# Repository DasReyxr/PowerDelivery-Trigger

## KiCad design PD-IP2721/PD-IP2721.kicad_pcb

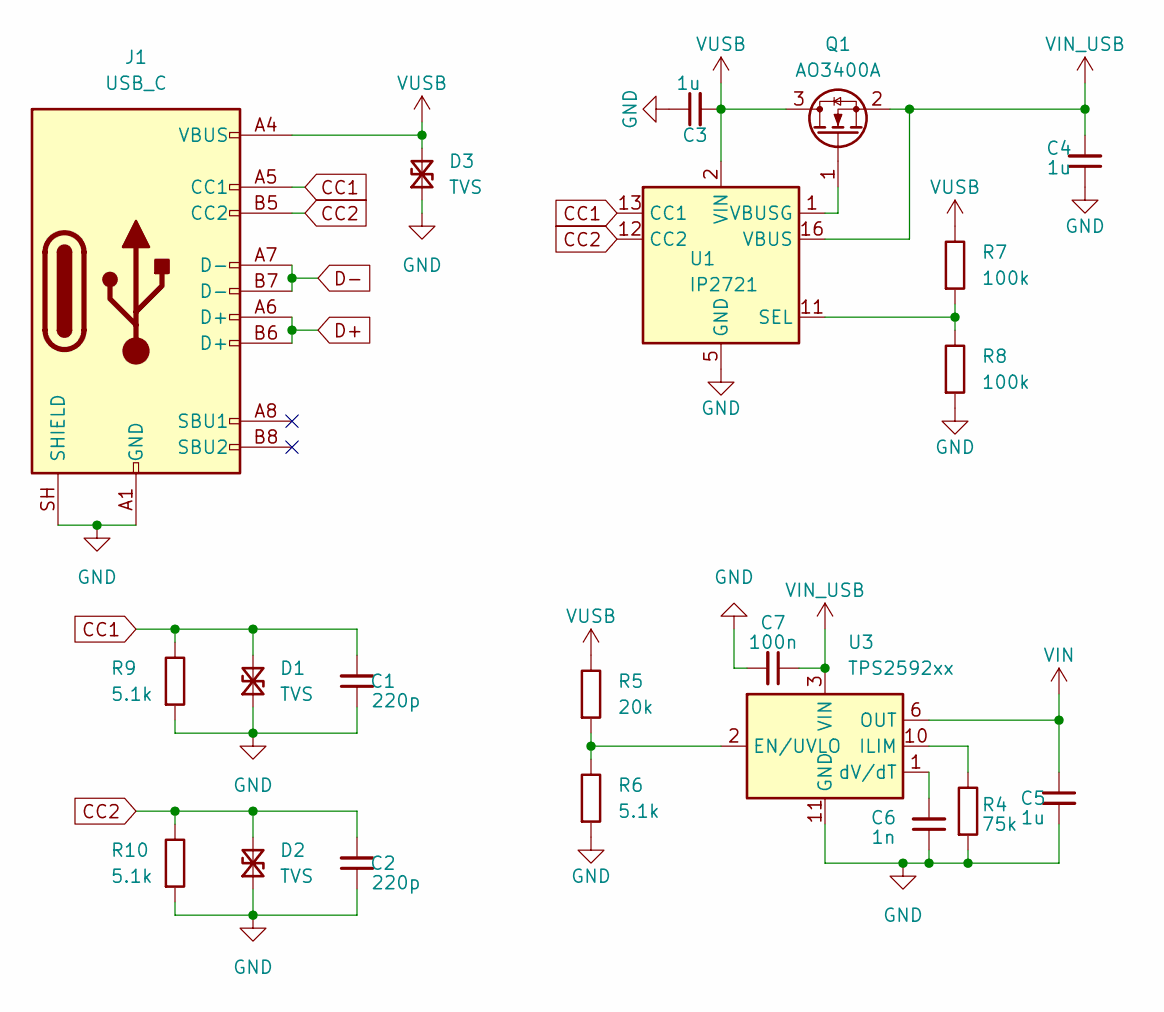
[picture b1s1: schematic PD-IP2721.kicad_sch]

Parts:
C1, C2: 220p; C_0603
C3, C4, C5: 1u; C_0603
C6: 1n; C_0603
C7: 100n; C_0603
D1, D2, D3: TVS; D_SOD-323
J1: USB_C; USB_C_Receptacle_JAE_DX07S016JA1R1500
Q1: AO3400A; SOT-23
R4: 75k; R_0603_1608Metric
R5: 20k; R_0603_1608Metric
R6, R9, R10: 5.1k; R_0603_1608Metric
R7, R8: 100k; R_0603_1608Metric
U1: IP2721; TSSOP-16_4.4x5mm_P0.65mm
U3: TPS2592xx; VSON-10-1EP_3x3mm_P0.5mm_EP1.65x2.4mm_ThermalVias

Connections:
CC1: C1.2, D1.2 (A2), J1.A5 (CC1), R9.2, U1.13 (CC1)
CC2: C2.2, D2.2 (A2), J1.B5 (CC2), R10.2, U1.12 (CC2)
D+: J1.A6 (D+), J1.B6 (D+)
D-: J1.A7 (D-), J1.B7 (D-)
GND: C1.1, C2.1, C3.1, C4.1, C5.2, C6.1, C7.2, D1.1 (A1), D2.1 (A1), D3.1 (A1), J1.A1 (GND), J1.A12 (GND), J1.B1 (GND), J1.B12 (GND), J1.SH (SHIELD), R4.1, R6.1, R8.1, R9.1, R10.1, U1.5 (GND), U3.11 (GND)
unnamed: Q1.1 (G), U1.1 (VBUSG)
unnamed: R7.1, R8.2, U1.11 (SEL)
unnamed: R5.1, R6.2, U3.2 (EN/UVLO)
unnamed: R4.2, U3.10 (ILIM)
unnamed: C6.2, U3.1 (dV/dT)
VIN: C5.1, U3.6 (OUT), U3.7 (OUT), U3.8 (OUT)
VIN_USB: C4.2, C7.1, Q1.2 (S), U1.16 (VBUS), U3.3 (VIN), U3.4 (VIN), U3.5 (VIN)
VUSB: C3.2, D3.2 (A2), J1.A4 (VBUS), J1.A9 (VBUS), J1.B4 (VBUS), J1.B9 (VBUS), Q1.3 (D), R5.2, R7.2, U1.2 (VIN)

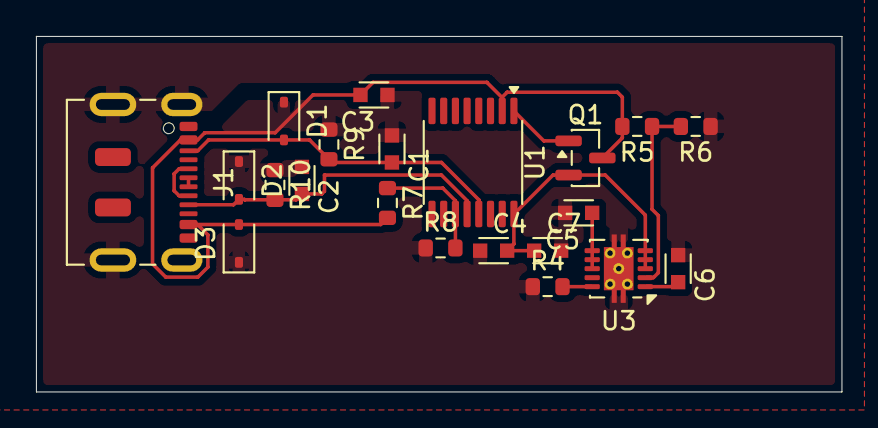
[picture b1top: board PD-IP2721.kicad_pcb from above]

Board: 2 copper layers, 44.8 x 19.8 mm, 21 parts (0 on the bottom side), 13 nets.

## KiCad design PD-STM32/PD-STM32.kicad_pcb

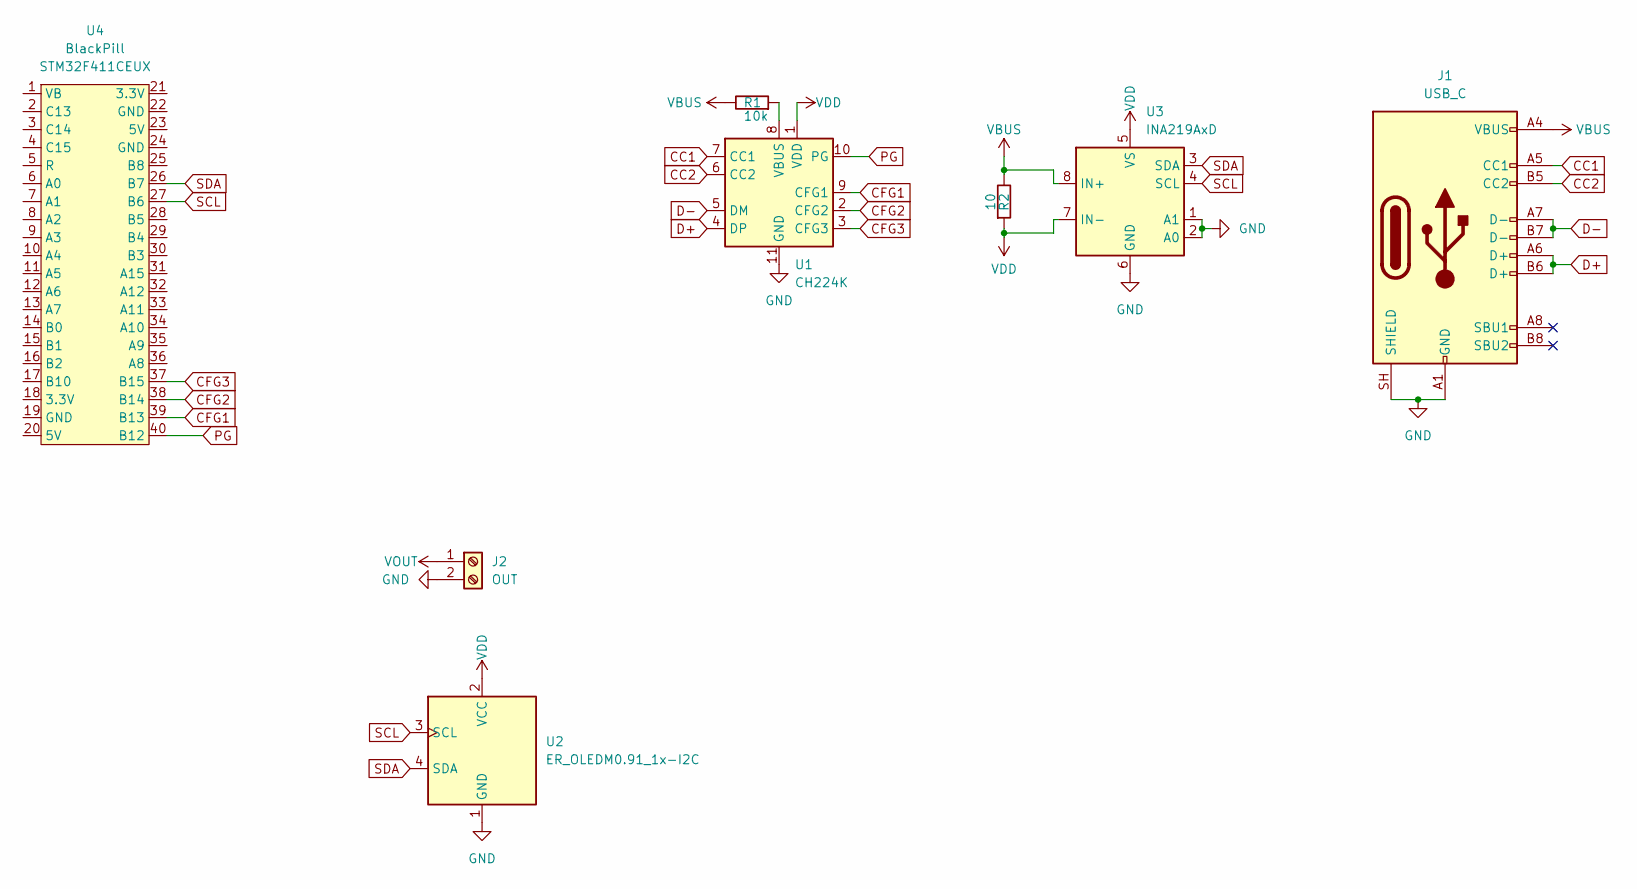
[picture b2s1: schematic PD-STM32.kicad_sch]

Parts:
J1: USB_C; USB_C_Receptacle_JAE_DX07S016JA1R1500
J2: OUT; TerminalBlock_OnShore_1x02_P3.50mm_Horizontal
R1: 10k; R_Axial_DIN0207_L6.3mm_D2.5mm_P10.16mm_Horizontal
R2: 10; R_Axial_DIN0207_L6.3mm_D2.5mm_P10.16mm_Horizontal
U1: CH224K; SSOP-10-1EP_3.9x4.9mm_P1mm_EP2.1x3.3mm
U2: ER_OLEDM0.91_1x-I2C
U3: INA219AxD; SOIC-8_3.9x4.9mm_P1.27mm
U4: BlackPill

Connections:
CC1: J1.A5 (CC1), U1.7 (CC1)
CC2: J1.B5 (CC2), U1.6 (CC2)
CFG1: U1.9 (CFG1), U4.39 (B13)
CFG2: U1.2 (CFG2), U4.38 (B14)
CFG3: U1.3 (CFG3), U4.37 (B15)
D+: J1.A6 (D+), J1.B6 (D+), U1.4 (DP)
D-: J1.A7 (D-), J1.B7 (D-), U1.5 (DM)
GND: J1.A1 (GND), J1.A12 (GND), J1.B1 (GND), J1.B12 (GND), J1.SH (SHIELD), J2.2, U1.11 (GND), U2.1 (GND), U3.1 (A1), U3.2 (A0), U3.6 (GND)
unnamed: R1.1, U1.8 (VBUS)
PG: U1.10 (PG), U4.40 (B12)
SCL: U2.3 (SCL), U3.4 (SCL), U4.27 (B6)
SDA: U2.4 (SDA), U3.3 (SDA), U4.26 (B7)
VBUS: J1.A4 (VBUS), J1.A9 (VBUS), J1.B4 (VBUS), J1.B9 (VBUS), R1.2, R2.2, U3.8 (IN+)
VDD: R2.1, U1.1 (VDD), U2.2 (VCC), U3.5 (VS), U3.7 (IN-)
VOUT: J2.1

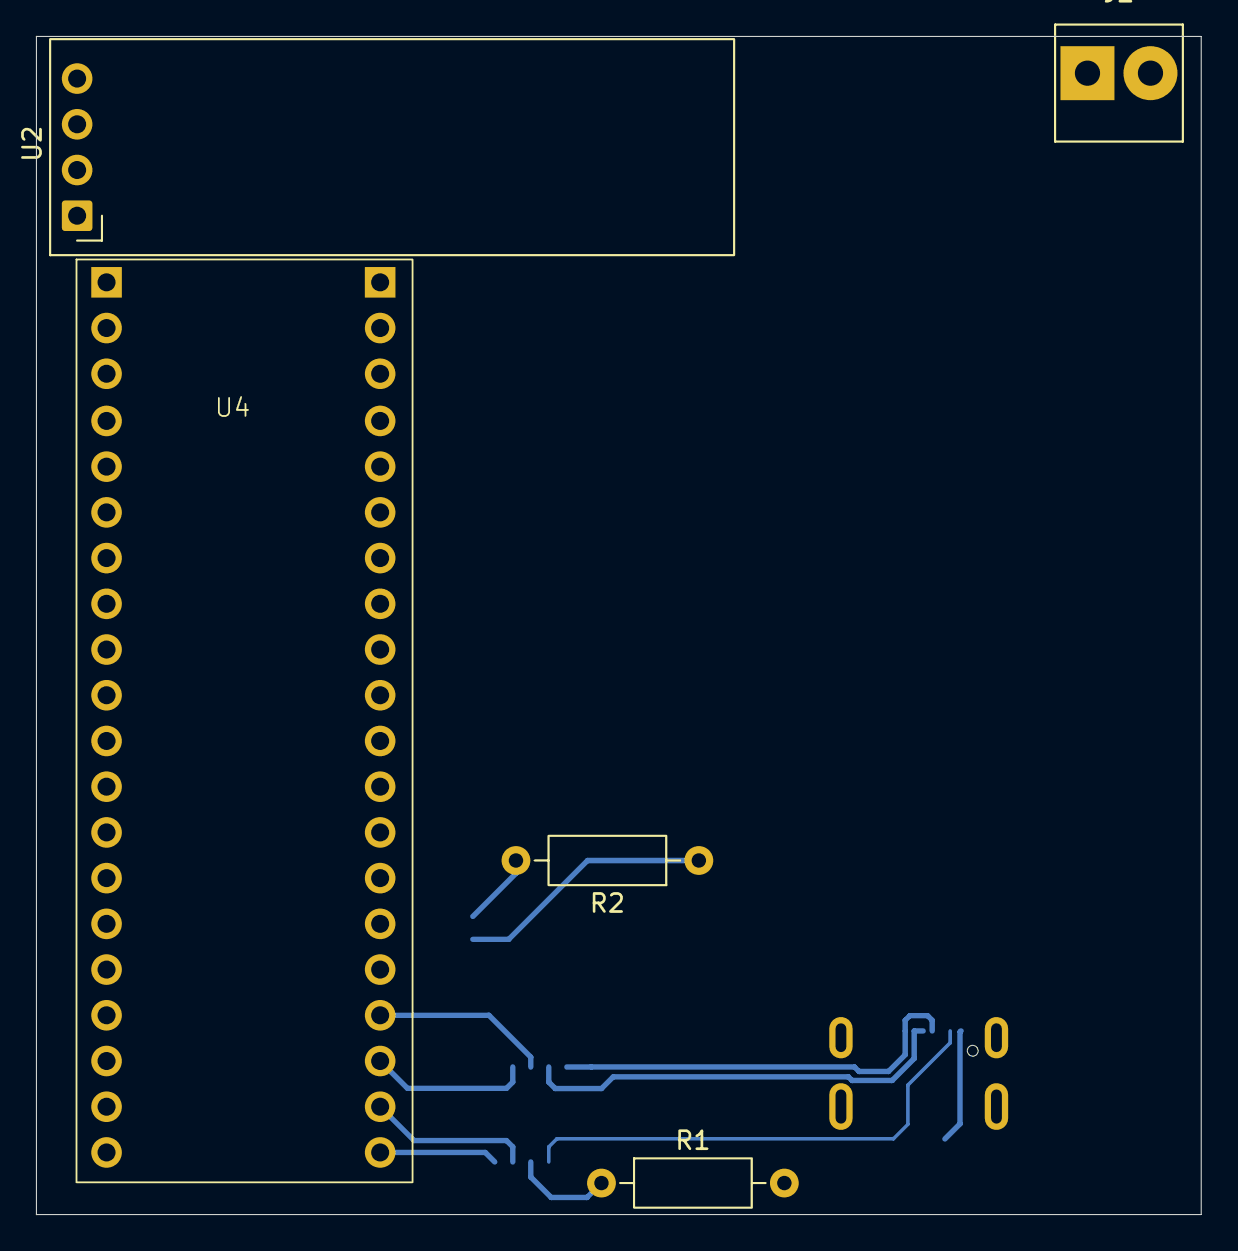
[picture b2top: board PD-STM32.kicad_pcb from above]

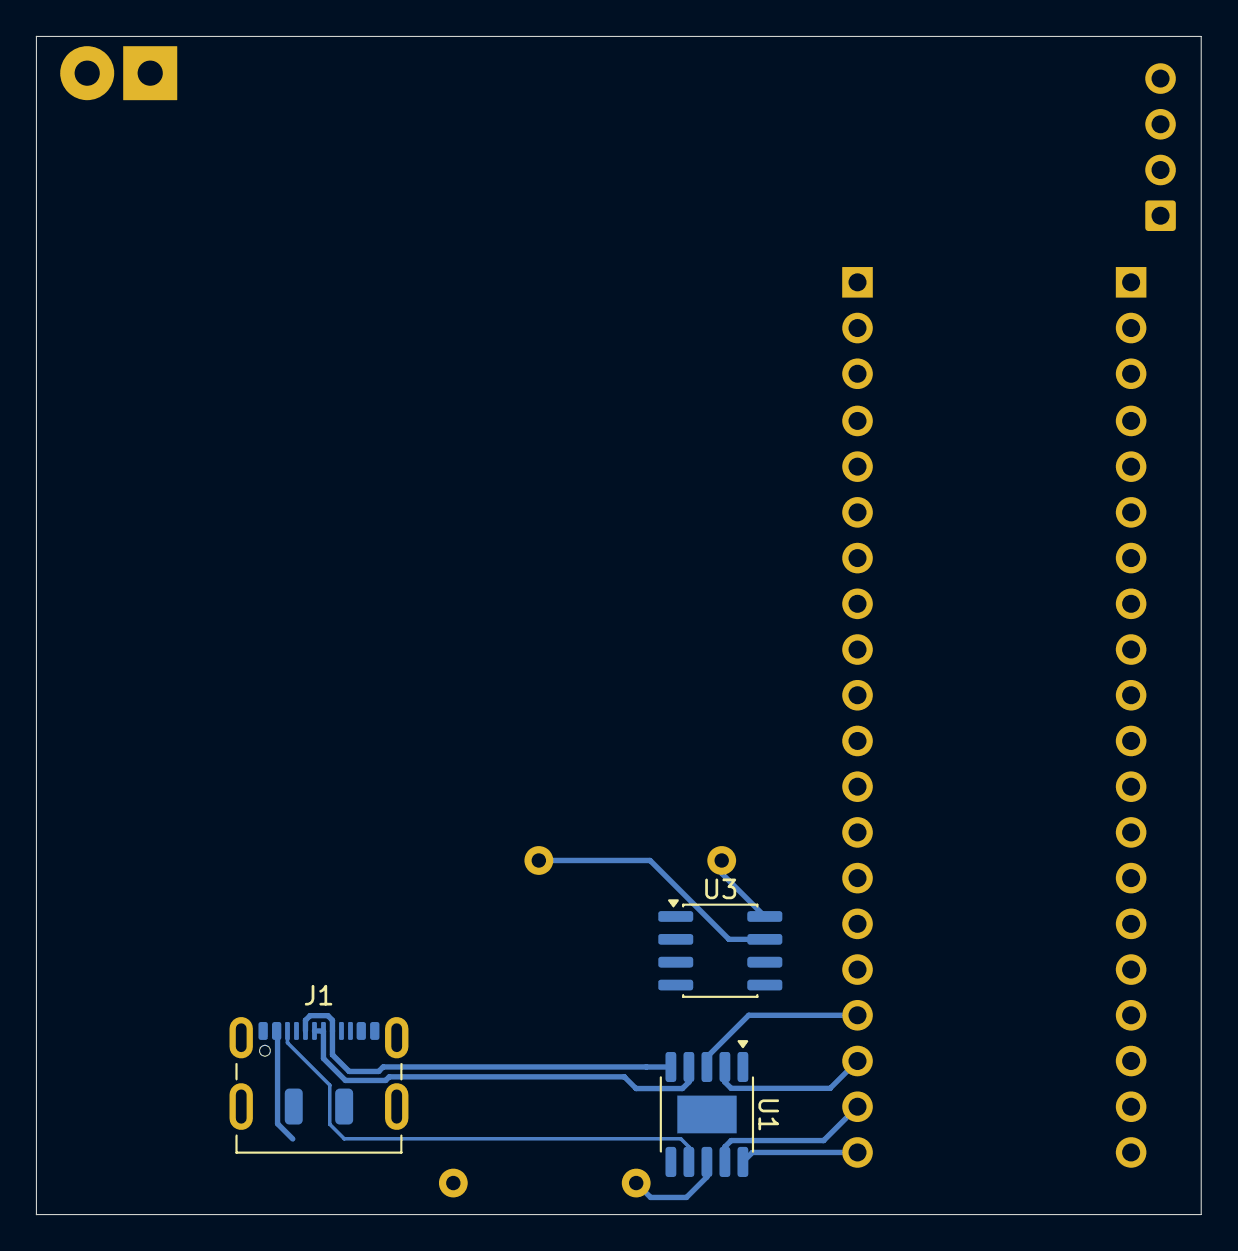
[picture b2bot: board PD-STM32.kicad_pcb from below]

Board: 2 copper layers, 64.7 x 65.5 mm, 8 parts (3 on the bottom side), 14 nets.
